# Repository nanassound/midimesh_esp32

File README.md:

# midiMESH ESP32

Open-source modular MIDI devices ecosystem over WiFi using ESP32-C3 and AtomVM. Control your DAW and devices wirelessly with various hardware controllers.

**Key Features:**
- MIDI CC messages over UDP/WiFi
- Concurrent multi-knob support with Elixir processes
- Operational in AP mode or STA mode
- Modular hardware designs (Eurorack-compatible)
- Runs AtomVM (Erlang VM) on ESP32-C3

**Demos:**
- [Controlling Arturia Pigments](https://www.youtube.com/shorts/djaUUPquI_E)
- [Knob Control in Ableton Live](https://www.youtube.com/shorts/GX_Sy0ogvio)
- [Use AP mode to sync tempo and beat in Link-enabled apps between multiple devices](https://www.youtube.com/shorts/Eo4ck_zq9FM)

## Project Structure

```
midimesh_esp32/
├── firmware/     # Elixir/AtomVM firmware for ESP32-C3
└── hardware/     # KiCad PCB design files for midiMESH devices
```

This repository contains both the firmware and hardware designs for the midiMESH ecosystem.

- **Firmware**: See [`firmware/`](firmware/) for the Elixir code that runs on the ESP32-C3. Detailed build, flash, and configuration instructions are in [`firmware/README.md`](firmware/README.md).
- **Hardware**: See [`hardware/`](hardware/) for various midiMESH device designs. Each subdirectory contains KiCad design files for a specific controller.

## Firmware

The firmware is written in Elixir and runs on [AtomVM](https://github.com/atomvm/AtomVM), a lightweight Erlang VM for embedded systems.

**Features:**
- Supports multiple analog potentiometers with concurrent processing
- Sends MIDI CC (Control Change) messages over UDP
- LED indicator for WiFi connection status
- Broadcasts to local network on port 4000
- Modular architecture with separate modules for Knob, Switch, MIDI operations, and Config

**Hardware pins** (configurable in code):
- Knob 1: GPIO 0
- Knob 2: GPIO 1
- LED: GPIO 8

For complete setup instructions, WiFi configuration, building, and flashing, see **[`firmware/README.md`](firmware/README.md)**.

## Hardware

The midiMESH ecosystem includes various Eurorack-compatible MIDI controller designs, each tailored for different control needs.

**Available Designs:**
- **Slide & Twist**: Controller with knobs and slide potentiometer
- **Control Voltage (coming soon)**: Wireless MIDI to CV for Eurorack modular synth

**Design Files:**
- KiCad v9.0 schematics and PCB layouts
- Location: [`hardware/`](hardware/)
- Each device has its own subdirectory with complete design files

For detailed component information and specifications for each controller, see [`hardware/README.md`](hardware/README.md).

The design files are provided as-is for viewing, modification, and manufacturing.

## Getting Started

### Prerequisites

**For Firmware:**
- ESP32-C3 board (tested with SuperMini)
- [AtomVM v0.6.6](https://github.com/atomvm/AtomVM/releases/tag/v0.6.6)
- Elixir with [ExAtomVM](https://github.com/atomvm/ExAtomVM)
- esptool.py for flashing

**For Hardware:**
- KiCad 9.0 or later to view/edit design files

### Quick Start

1. **Flash firmware**: Follow the detailed instructions in [`firmware/README.md`](firmware/README.md) to configure WiFi, build, and flash the ESP32-C3.
2. **View hardware designs**: See [`hardware/README.md`](hardware/README.md) for available midiMESH devices. Open the KiCad project files to explore or modify the PCB designs.
3. **Receive MIDI**: Use the companion [midiMESH desktop receiver](https://github.com/nanassound/midimesh_desktop_receiver) to receive UDP MIDI and forward it to a virtual MIDI port for use in your DAW.

## Related Projects

- **[midimesh_desktop_receiver](https://github.com/nanassound/midimesh_desktop_receiver)**: Desktop application that receives UDP MIDI messages from the ESP32 and forwards them to a virtual MIDI port (e.g., IAC Driver on macOS).

## License

This project is dual-licensed:

### Firmware License

The firmware (in [`firmware/`](firmware/)) is licensed under the **Apache 2.0 license**.

See [`firmware/LICENSE.md`](firmware/LICENSE.md) for full license text.

### Hardware License

The hardware design (in [`hardware/`](hardware/)) is licensed under the **CERN Open Hardware License v2 - Weakly Reciprocal (CERN-OHL-W)**.

See [`hardware/LICENSE.md`](hardware/LICENSE.md) for full license text.

### Derivative Works Guidelines

Both licenses allow you to freely use, study, modify, and distribute this project and create derivative works.

**Important:** You must **NOT** use the "Nanas Sound" name, logo, or any other Nanas Sound identifiers in your derivative works. Nanas Sound is a business name of [Nanas Sound OÜ](https://ariregister.rik.ee/est/company/16028176/Nanas-Sound-OÜ).

**Examples of acceptable naming:**
- **Correct**: "Strawberry Field - MIDIYummy"
- **Incorrect**: "Nanas Sound's midiMESH" or "Based on Nanas Sound midiMESH"

We encourage you to create and share your own versions of this project while respecting our trademark.

## Contributing

Contributions, issues, and feature requests are welcome. Feel free to open an issue or submit a pull request.

---

**Copyright 2025 Nanas Sound OÜ**

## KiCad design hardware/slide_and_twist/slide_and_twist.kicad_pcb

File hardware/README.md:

# midiMESH Hardware Designs

This directory contains KiCad design files for various midiMESH controllers. Each controller is a Eurorack-compatible MIDI device that works with the midiMESH firmware.

## Available Controllers

### Slide & Twist

**Description:** A versatile MIDI controller featuring both rotary knobs and a slide potentiometer for expressive control.

**Key Components:**
- ESP32-C3 SuperMini microcontroller
- 4 potentiometers (10k, B10K) - rotary knobs
- 1 slide potentiometer (PTL30-19G1-103B2)
- 1 SPDT sub-miniature toggle switch
- 1 LED (status indicator)
- 1 resistor (LED current limiting)
- Eurorack 16-pin shrouded power connector
- Pin headers for ESP32-C3 SuperMini

**Power Requirements:**
+5V from USB-C, Eurorack power header (J2), or adding battery to the power connector (J1)

**Design Files:**
- Location: [`slide_and_twist/`](slide_and_twist/)
- Schematic: `slide_and_twist.kicad_sch`
- PCB Layout: `slide_and_twist.kicad_pcb`
- Project File: `slide_and_twist.kicad_pro`

**KiCad Version:** 9.0

**Last Updated:** 2025-12-06

## Design Notes

All midiMESH controllers share common features:
- Eurorack form factor and power compatibility
- ESP32-C3 based for WiFi connectivity
- Designed to work with the midiMESH firmware (see [`firmware/`](../firmware/))
- Status LED for connection indication
- Modular and expandable design

## Using the Design Files

### Viewing and Editing

1. Install [KiCad 9.0](https://www.kicad.org/download/) or later
2. Open the `.kicad_pro` file in the respective controller directory
3. View schematics (`.kicad_sch`) and PCB layout (`.kicad_pcb`)

### Manufacturing

The design files are ready for PCB manufacturing. You can:
- Export Gerber files from KiCad for PCB fabrication
- Export BOM (Bill of Materials) for component ordering
- Export pick-and-place files for assembly (if needed)

**Note:** Assembly and manufacturing instructions are not provided. Users are expected to have basic PCB manufacturing and assembly knowledge.

## License

All hardware designs in this directory are licensed under the **CERN Open Hardware License v2 - Weakly Reciprocal (CERN-OHL-W)**.

Copyright 2025 Nanas Sound OÜ

See [`LICENSE.md`](LICENSE.md) for full license text.

### Derivative Works

You are free to modify and create derivative works. However, you must **NOT** use the "Nanas Sound" name, logo, or identifiers in your derivatives. See the main [project README](../README.md#derivative-works-guidelines) for details.

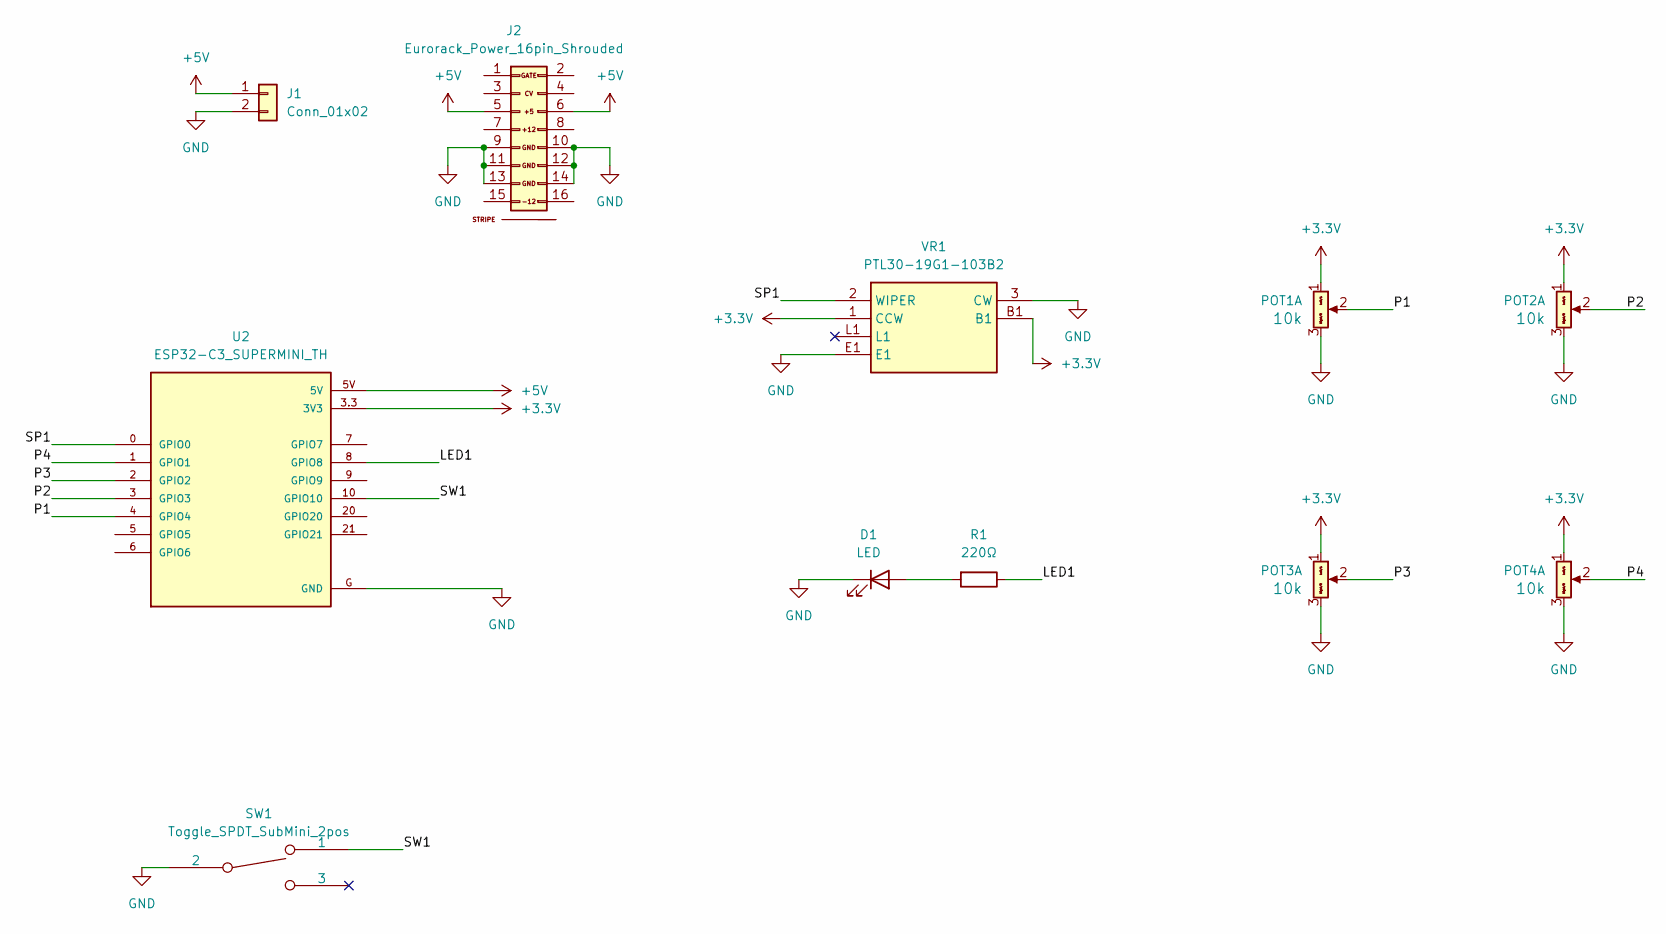
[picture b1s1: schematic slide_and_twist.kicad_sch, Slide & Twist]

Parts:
D1: LED; LED_D3.0mm_FlatTop
J1: Conn_01x02; Pins_1x02_2.54mm_TH; Part Number 1-0201FBV0T
J2: Eurorack_Power_16pin_Shrouded; Pins_2x08_2.54mm_TH_EuroPower_Shrouded; Part Number LL1007-1 (2*8 HITEMP)
POT1, POT2, POT3, POT4: 9mm_NoDet_10k_DShaft; Pot_9mm_DShaft; Part Number RV09BCF-40-25F-B10K-007
R1: 220Ω; R_Box_L13.0mm_W4.0mm_P9.00mm
SW1: Toggle_SPDT_SubMini_2pos; TestPoint_2Pads_Pitch2.54mm_Drill0.8mm; Part Number 200-MSP3-T2B3M2QE
U2: ESP32-C3_SUPERMINI_TH; MODULE_ESP32-C3_SUPERMINI_TH
VR1: PTL30-19G1-103B2; PTL3019G1103B2; Mouser Part Number 652-PTL30-19G1-103B2

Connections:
+3.3V: POT1.1 (Left), POT2.1 (Left), POT3.1 (Left), POT4.1 (Left), U2.3.3 (3V3), VR1.1 (CCW), VR1.B1
+5V: J1.1, J2.5 (+12V), J2.6, U2.5V
/LED1: R1.1, U2.8 (GPIO8)
/P1: POT1.2 (Center), U2.4 (GPIO4)
/P2: POT2.2 (Center), U2.3 (GPIO3)
/P3: POT3.2 (Center), U2.2 (GPIO2)
/P4: POT4.2 (Center), U2.1 (GPIO1)
/SP1: U2.0 (GPIO0), VR1.2 (WIPER)
/SW1: SW1.1, U2.10 (GPIO10)
GND: D1.1 (K), J1.2, J2.9 (GND), J2.10 (GND), J2.11 (GND), J2.12 (GND), J2.13 (-12), J2.14 (-12V), POT1.3 (Right), POT2.3 (Right), POT3.3 (Right), POT4.3 (Right), SW1.2, U2.G (GND), VR1.3 (CW), VR1.E1
unnamed: D1.2 (A), R1.2

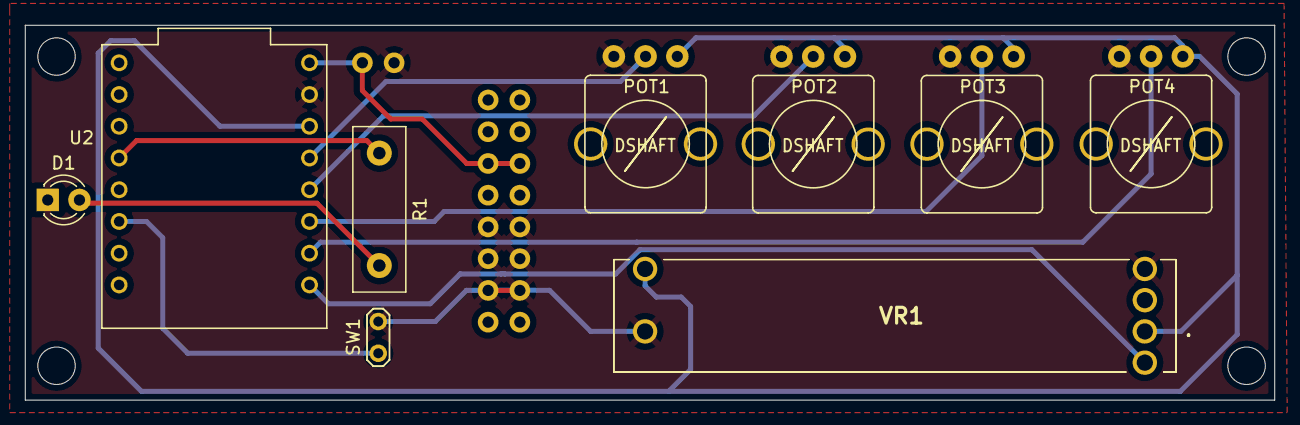
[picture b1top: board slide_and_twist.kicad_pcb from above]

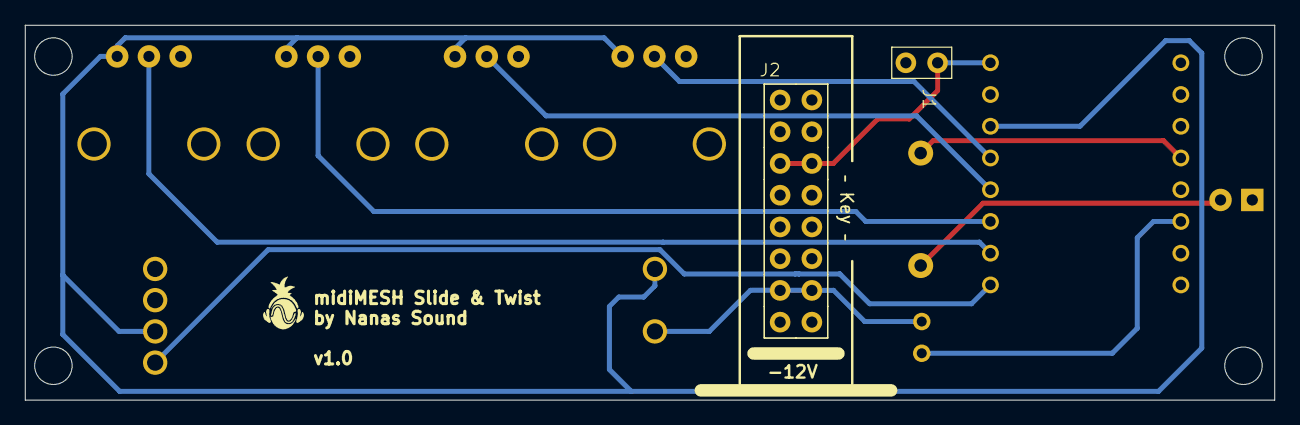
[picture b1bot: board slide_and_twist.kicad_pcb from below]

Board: 2 copper layers, 100.0 x 30.0 mm, 11 parts (2 on the bottom side), 11 nets.

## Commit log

2025-11-22 Making proof-of-concept
2025-11-22 Add the demo link
2025-11-24 Add knob functionality with analog potentiometer.
2025-11-24 Add knob functionality with analog potentiometer. (#1)
2025-11-25 Add how to flash in README.md
2025-11-26 Add multiple knobs capabilities
2025-11-26 Adding multiple knobs capabilities (#2)
    * Add how to flash in README.md
    * Add multiple knobs capabilities
2025-11-26 Add new YouTube demo
2025-11-28 Make Bela Trill reading the correct touch and position.
2025-11-29 Adding Bela Bar support
2025-12-04 Make the installation step easier with pythonx
2025-12-04 Make the installation step easier with pythonx (#3)
2025-12-05 Use receive to suspend the main process
2025-12-09 Adding "Slide & Twist" hardware design
2025-12-09 Adding "Slide & Twist" hardware design (#4)
2025-12-09 Adding PDF schematic
2025-12-10 Change to Apache 2.0 license
2025-12-10 Change to Apache 2.0 license (#5)
2025-12-10 Edit readme
2025-12-14 Refactor the network config code.
2025-12-14 Adding switches capability to choose AP/STA mode while booting.
2025-12-14 Remove unnecessary IO.puts
2025-12-14 Adding support for choosing between AP or STA mode by using switch (#6)
    * Refactor the network config code.
    * Adding switches capability to choose AP/STA mode while booting.
    * Remove unnecessary IO.puts
2025-12-19 Restructuring the process and message passing in AP mode.
2025-12-19 Fixing the network config format
2025-12-19 Restructure the knob process and UDP sender process (#7)
    * Restructuring the process and message passing in AP mode.
    * Fixing the network config format
2025-12-20 Use "alias" to make less repetition
2025-12-20 Use "alias" to make less repetition (#8)
2025-12-20 Update readme.
2025-12-23 Implementing gen_statem
2025-12-23 Implementing gen_statem to monitor the AP/STA mode switch
2025-12-23 Auto restart the device when users change the state of the AP/STA mode switch (#9)
    * Implementing gen_statem
    * Implementing gen_statem to monitor the AP/STA mode switch
